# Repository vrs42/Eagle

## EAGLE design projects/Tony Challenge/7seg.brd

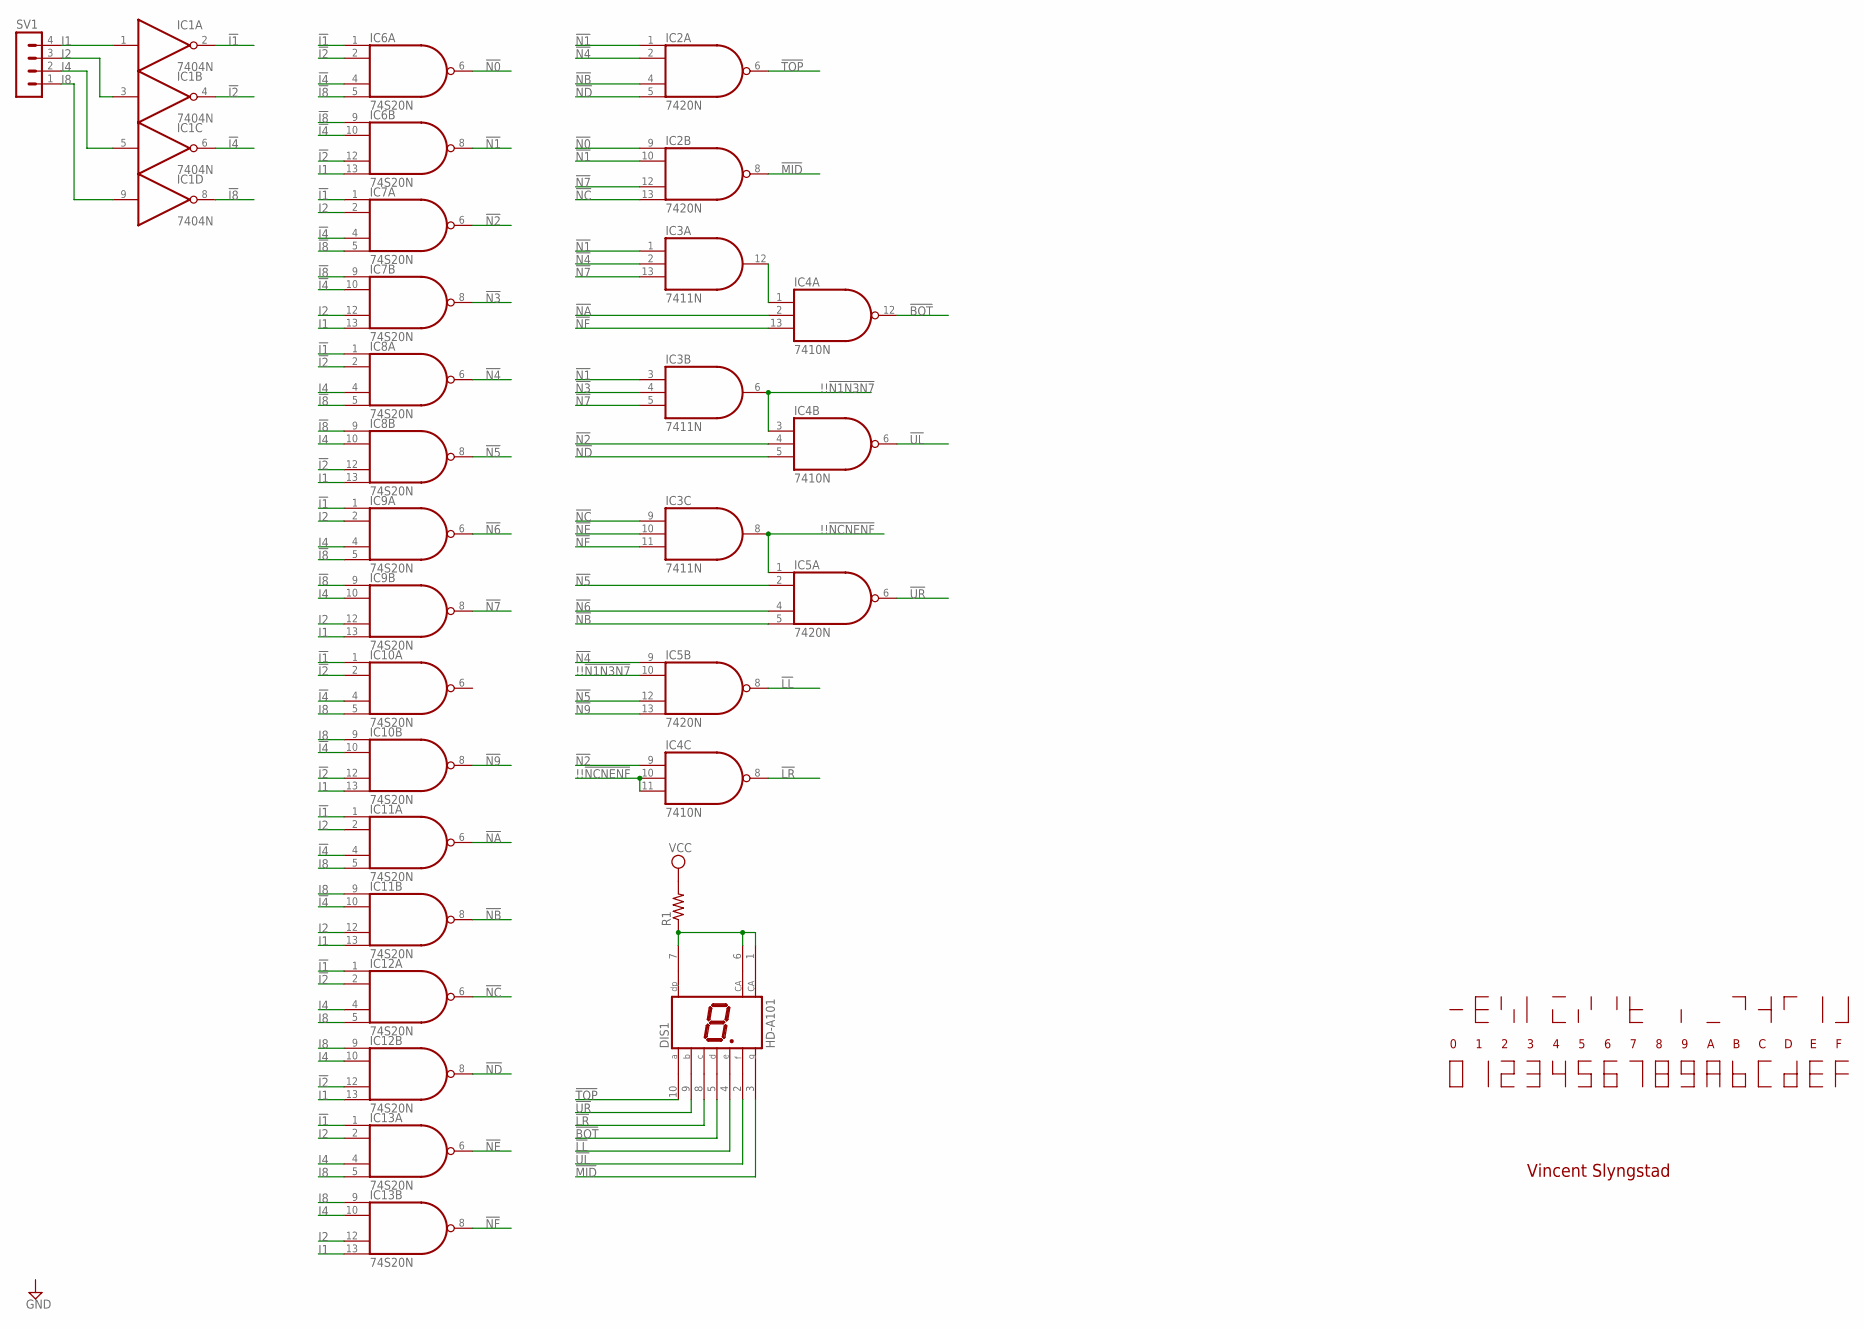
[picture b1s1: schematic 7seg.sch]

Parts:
DIS1: HD-A101; HDSP-A
IC1: 7404N; DIL14
IC2, IC5: 7420N; DIL14
IC3: 7411N; DIL14
IC4: 7410N; DIL14
IC6, IC7, IC8, IC9, IC10, IC11, IC12, IC13: 74S20N; DIL14
R1: R-US_0207/10; 0207/10
SV1: MA04-1

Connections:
!!!N1N3N7: IC3.6 (O), IC4.3 (I0), IC5.10 (I1)
!!!NCNENF: IC3.8 (O), IC4.10 (I1), IC4.11 (I2), IC5.1 (I0)
!BOT: DIS1.5 (D), IC4.12 (O)
!I1: IC1.2 (O), IC6.1 (I0), IC7.1 (I0), IC8.1 (I0), IC9.1 (I0), IC10.1 (I0), IC11.1 (I0), IC12.1 (I0), IC13.1 (I0)
!I2: IC1.4 (O), IC6.2 (I1), IC6.12 (I2), IC8.2 (I1), IC8.12 (I2), IC10.2 (I1), IC10.12 (I2), IC12.2 (I1), IC12.12 (I2)
!I4: IC1.6 (O), IC6.4 (I2), IC6.10 (I1), IC7.4 (I2), IC7.10 (I1), IC10.4 (I2), IC10.10 (I1), IC11.4 (I2), IC11.10 (I1)
!I8: IC1.8 (O), IC6.5 (I3), IC6.9 (I0), IC7.5 (I3), IC7.9 (I0), IC8.5 (I3), IC8.9 (I0), IC9.5 (I3), IC9.9 (I0)
!LL: DIS1.4 (E), IC5.8 (O)
!LR: DIS1.8 (C), IC4.8 (O)
!MID: DIS1.3 (G), IC2.8 (O)
!N0: IC2.9 (I0), IC6.6 (O)
!N1: IC2.1 (I0), IC2.10 (I1), IC3.1 (I0), IC3.3 (I0), IC6.8 (O)
!N2: IC4.4 (I1), IC4.9 (I0), IC7.6 (O)
!N3: IC3.4 (I1), IC7.8 (O)
!N4: IC2.2 (I1), IC3.2 (I1), IC5.9 (I0), IC8.6 (O)
!N5: IC5.2 (I1), IC5.12 (I2), IC8.8 (O)
!N6: IC5.4 (I2), IC9.6 (O)
!N7: IC2.12 (I2), IC3.5 (I2), IC3.13 (I2), IC9.8 (O)
!N9: IC5.13 (I3), IC10.8 (O)
!NA: IC4.2 (I1), IC11.6 (O)
!NB: IC2.4 (I2), IC5.5 (I3), IC11.8 (O)
!NC: IC2.13 (I3), IC3.9 (I0), IC12.6 (O)
!ND: IC2.5 (I3), IC4.5 (I2), IC12.8 (O)
!NE: IC3.10 (I1), IC13.6 (O)
!NF: IC3.11 (I2), IC4.13 (I2), IC13.8 (O)
!TOP: DIS1.10 (A), IC2.6 (O)
!UL: DIS1.2 (F), IC4.6 (O)
!UR: DIS1.9 (B), IC5.6 (O)
GND: IC1.7 (GND), IC2.7 (GND), IC3.7 (GND), IC4.7 (GND), IC5.7 (GND), IC6.7 (GND), IC7.7 (GND), IC8.7 (GND), IC9.7 (GND), IC10.7 (GND), IC11.7 (GND), IC12.7 (GND), IC13.7 (GND)
I1: IC1.1 (I), IC6.13 (I3), IC7.13 (I3), IC8.13 (I3), IC9.13 (I3), IC10.13 (I3), IC11.13 (I3), IC12.13 (I3), IC13.13 (I3), SV1.4
I2: IC1.3 (I), IC7.2 (I1), IC7.12 (I2), IC9.2 (I1), IC9.12 (I2), IC11.2 (I1), IC11.12 (I2), IC13.2 (I1), IC13.12 (I2), SV1.3
I4: IC1.5 (I), IC8.4 (I2), IC8.10 (I1), IC9.4 (I2), IC9.10 (I1), IC12.4 (I2), IC12.10 (I1), IC13.4 (I2), IC13.10 (I1), SV1.2
I8: IC1.9 (I), IC10.5 (I3), IC10.9 (I0), IC11.5 (I3), IC11.9 (I0), IC12.5 (I3), IC12.9 (I0), IC13.5 (I3), IC13.9 (I0), SV1.1
unnamed: IC3.12 (O), IC4.1 (I0)
unnamed: DIS1.1 (CA), DIS1.6 (CA), DIS1.7 (DP), R1.1
VCC: IC1.14 (VCC), IC2.14 (VCC), IC3.14 (VCC), IC4.14 (VCC), IC5.14 (VCC), IC6.14 (VCC), IC7.14 (VCC), IC8.14 (VCC), IC9.14 (VCC), IC10.14 (VCC), IC11.14 (VCC), IC12.14 (VCC), IC13.14 (VCC), R1.2

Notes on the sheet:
Vincent Slyngstad

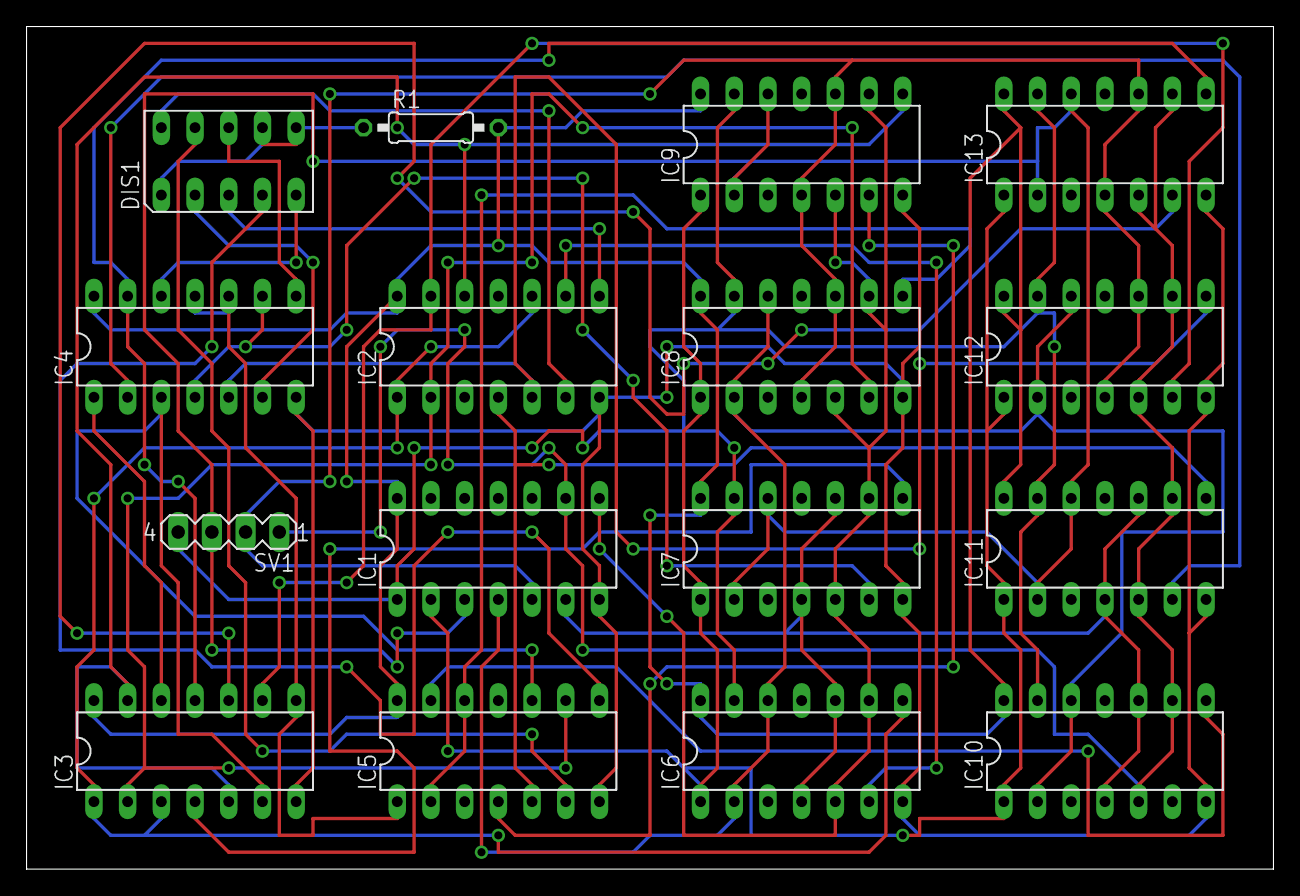
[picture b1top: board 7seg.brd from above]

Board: 2 copper layers, 94.0 x 63.5 mm, 16 parts (0 on the bottom side), 36 nets.

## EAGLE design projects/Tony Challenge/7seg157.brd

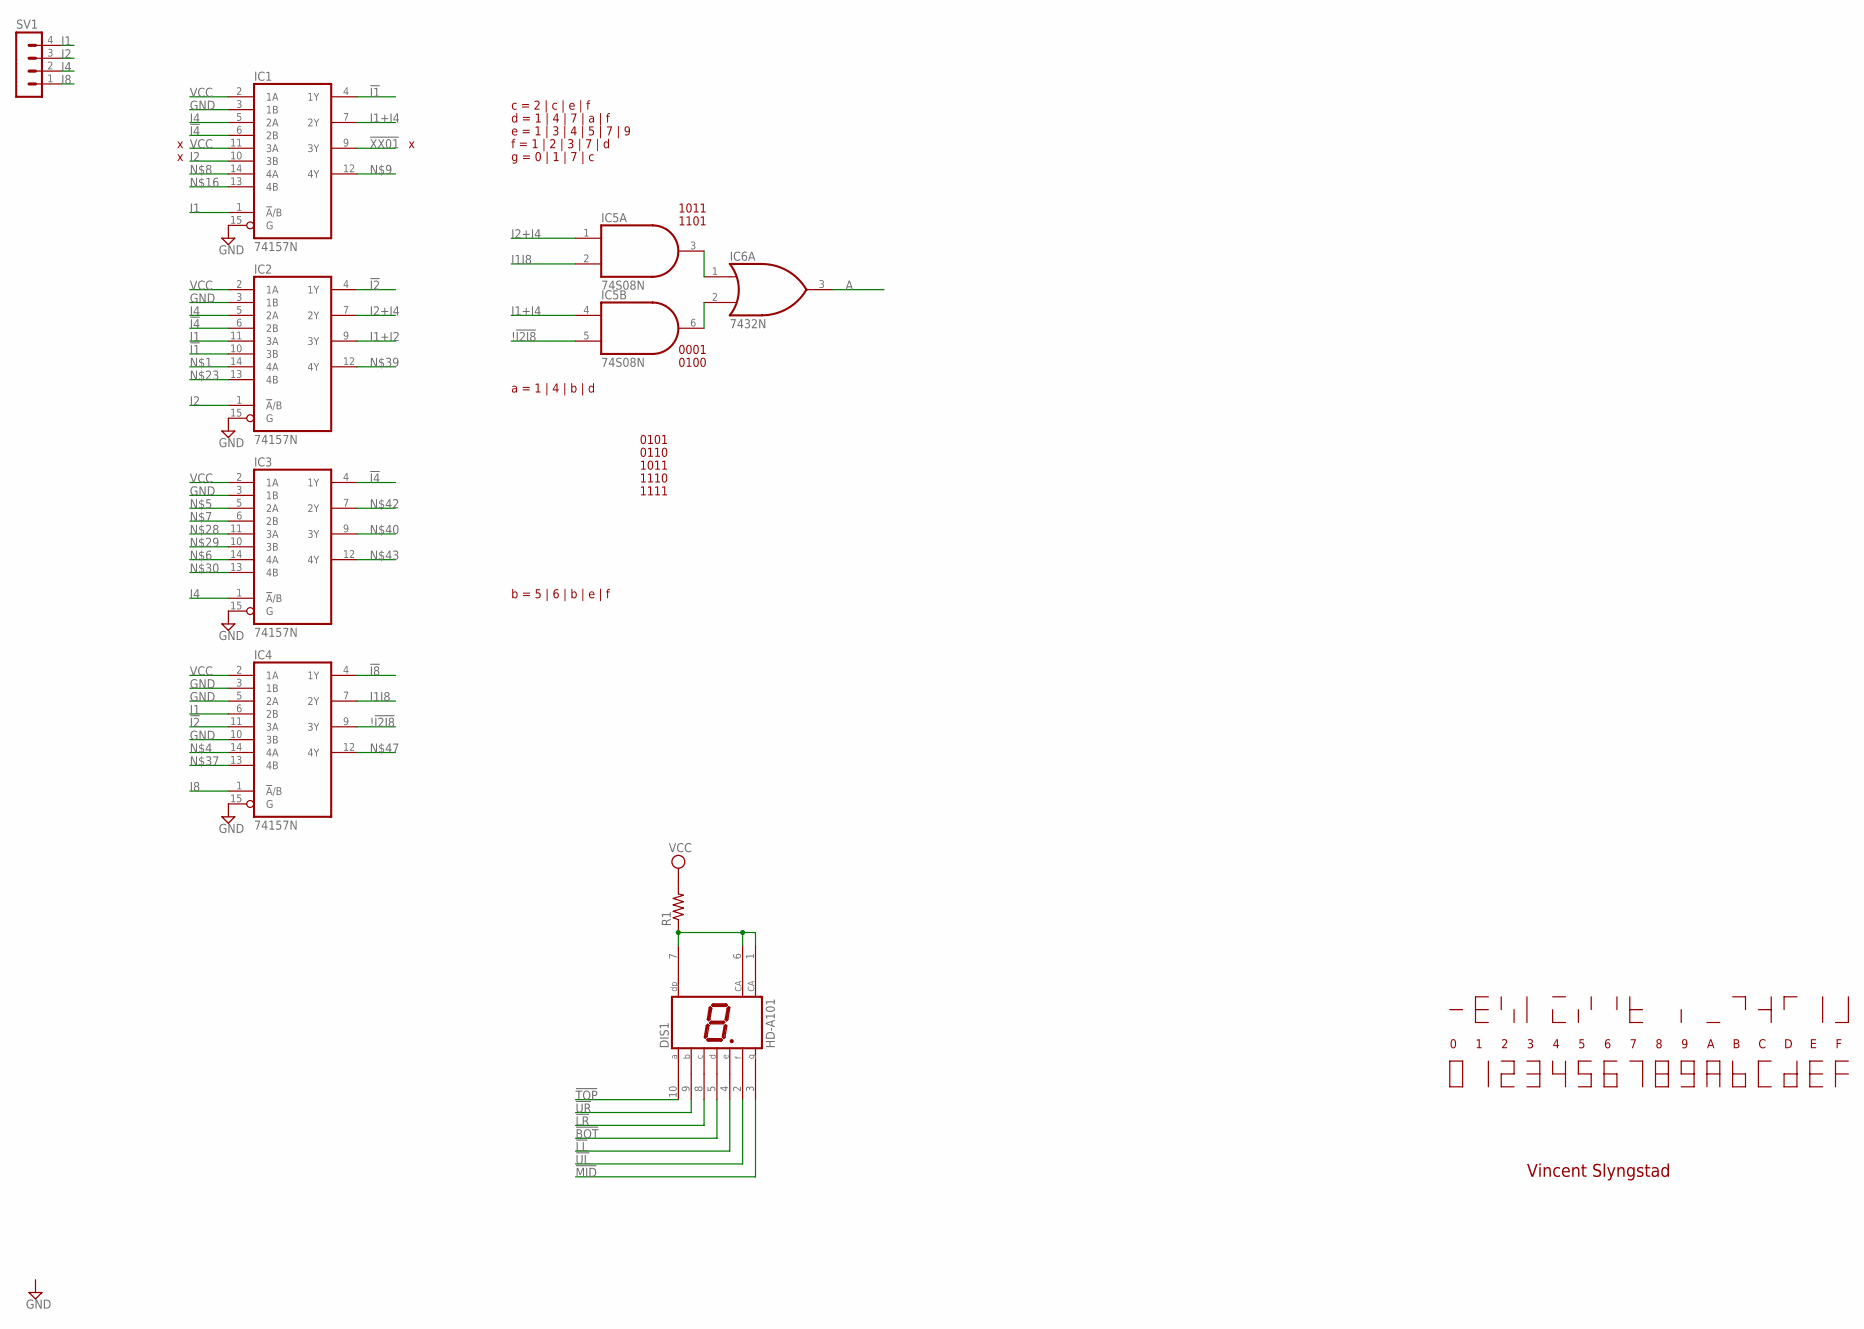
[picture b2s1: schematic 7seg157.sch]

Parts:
DIS1: HD-A101; HDSP-A
IC1, IC2, IC3, IC4: 74157N; DIL16
IC5: 74S08N; DIL14
IC6: 7432N; DIL14
R1: R-US_0207/10; 0207/10
SV1: MA04-1

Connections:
!!I2I8: IC4.9 (3Y), IC5.5 (I1)
!BOT: DIS1.5 (D)
!I1: IC1.4 (1Y), IC2.10 (3B)
!I2: IC2.4 (1Y), IC4.11 (3A)
!I4: IC1.6 (2B), IC2.6 (2B), IC3.4 (1Y)
!I8: IC4.4 (1Y)
!LL: DIS1.4 (E)
!LR: DIS1.8 (C)
!MID: DIS1.3 (G)
!TOP: DIS1.10 (A)
!UL: DIS1.2 (F)
!UR: DIS1.9 (B)
!XX01: IC1.9 (3Y)
A: IC6.3 (O)
GND: IC1.3 (1B), IC1.8 (GND), IC1.15 (G), IC2.3 (1B), IC2.8 (GND), IC2.15 (G), IC3.3 (1B), IC3.8 (GND), IC3.15 (G), IC4.3 (1B), IC4.5 (2A), IC4.8 (GND), IC4.10 (3B), IC4.15 (G), IC5.7 (GND), IC6.7 (GND)
I1: IC1.1 (!A!/B), IC2.11 (3A), IC4.6 (2B), SV1.4
I1+I2: IC2.9 (3Y)
I1+I4: IC1.7 (2Y), IC5.4 (I0)
I1I8: IC4.7 (2Y), IC5.2 (I1)
I2: IC1.10 (3B), IC2.1 (!A!/B), SV1.3
I2+I4: IC2.7 (2Y), IC5.1 (I0)
I4: IC1.5 (2A), IC2.5 (2A), IC3.1 (!A!/B), SV1.2
I8: IC4.1 (!A!/B), SV1.1
unnamed: DIS1.1 (CA), DIS1.6 (CA), DIS1.7 (DP), R1.1
unnamed: IC5.3 (O), IC6.1 (I0)
unnamed: IC5.6 (O), IC6.2 (I1)
VCC: IC1.2 (1A), IC1.11 (3A), IC1.16 (VCC), IC2.2 (1A), IC2.16 (VCC), IC3.2 (1A), IC3.16 (VCC), IC4.2 (1A), IC4.16 (VCC), IC5.14 (VCC), IC6.14 (VCC), R1.2

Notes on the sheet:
Vincent Slyngstad
a = 1 | 4 | b | d
b = 5 | 6 | b | e | f
c = 2 | c | e | f
d = 1 | 4 | 7 | a | f
e = 1 | 3 | 4 | 5 | 7 | 9
f = 1 | 2 | 3 | 7 | d
g = 0 | 1 | 7 | c
0001
0100
1011
1101
0101
0110
1110
1111

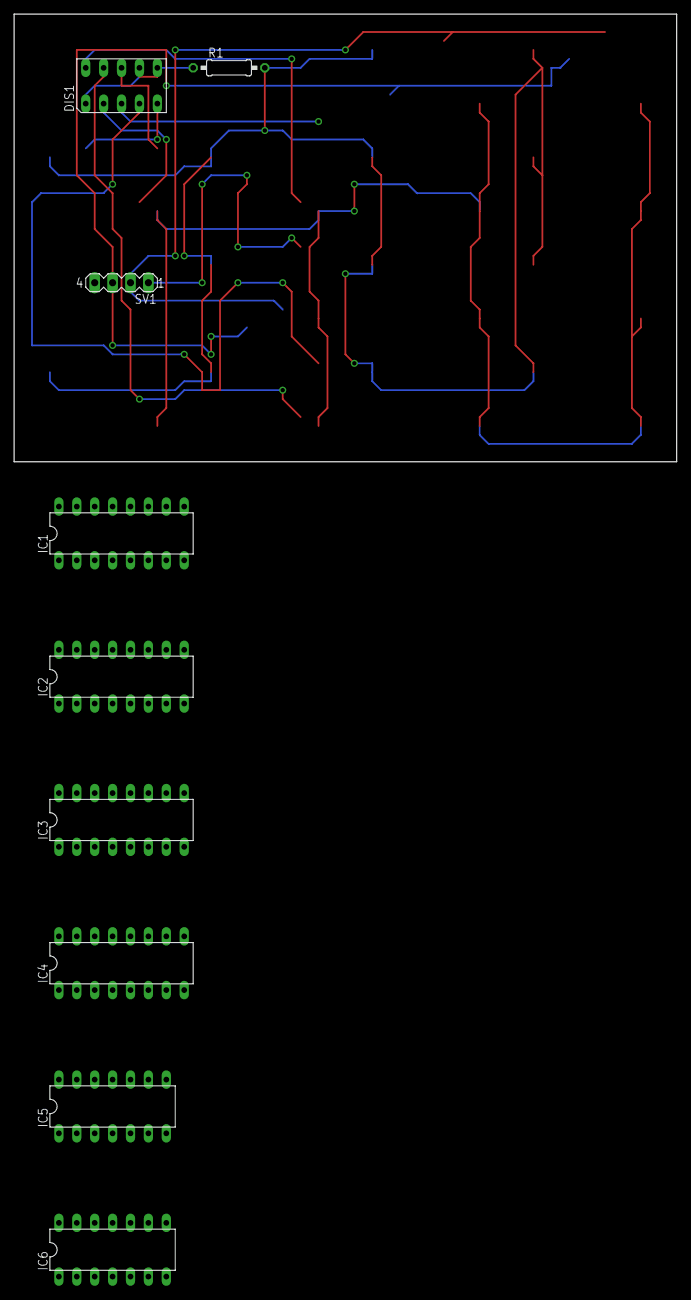
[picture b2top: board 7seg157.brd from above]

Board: 2 copper layers, 94.0 x 63.5 mm, 9 parts (0 on the bottom side), 16 nets.

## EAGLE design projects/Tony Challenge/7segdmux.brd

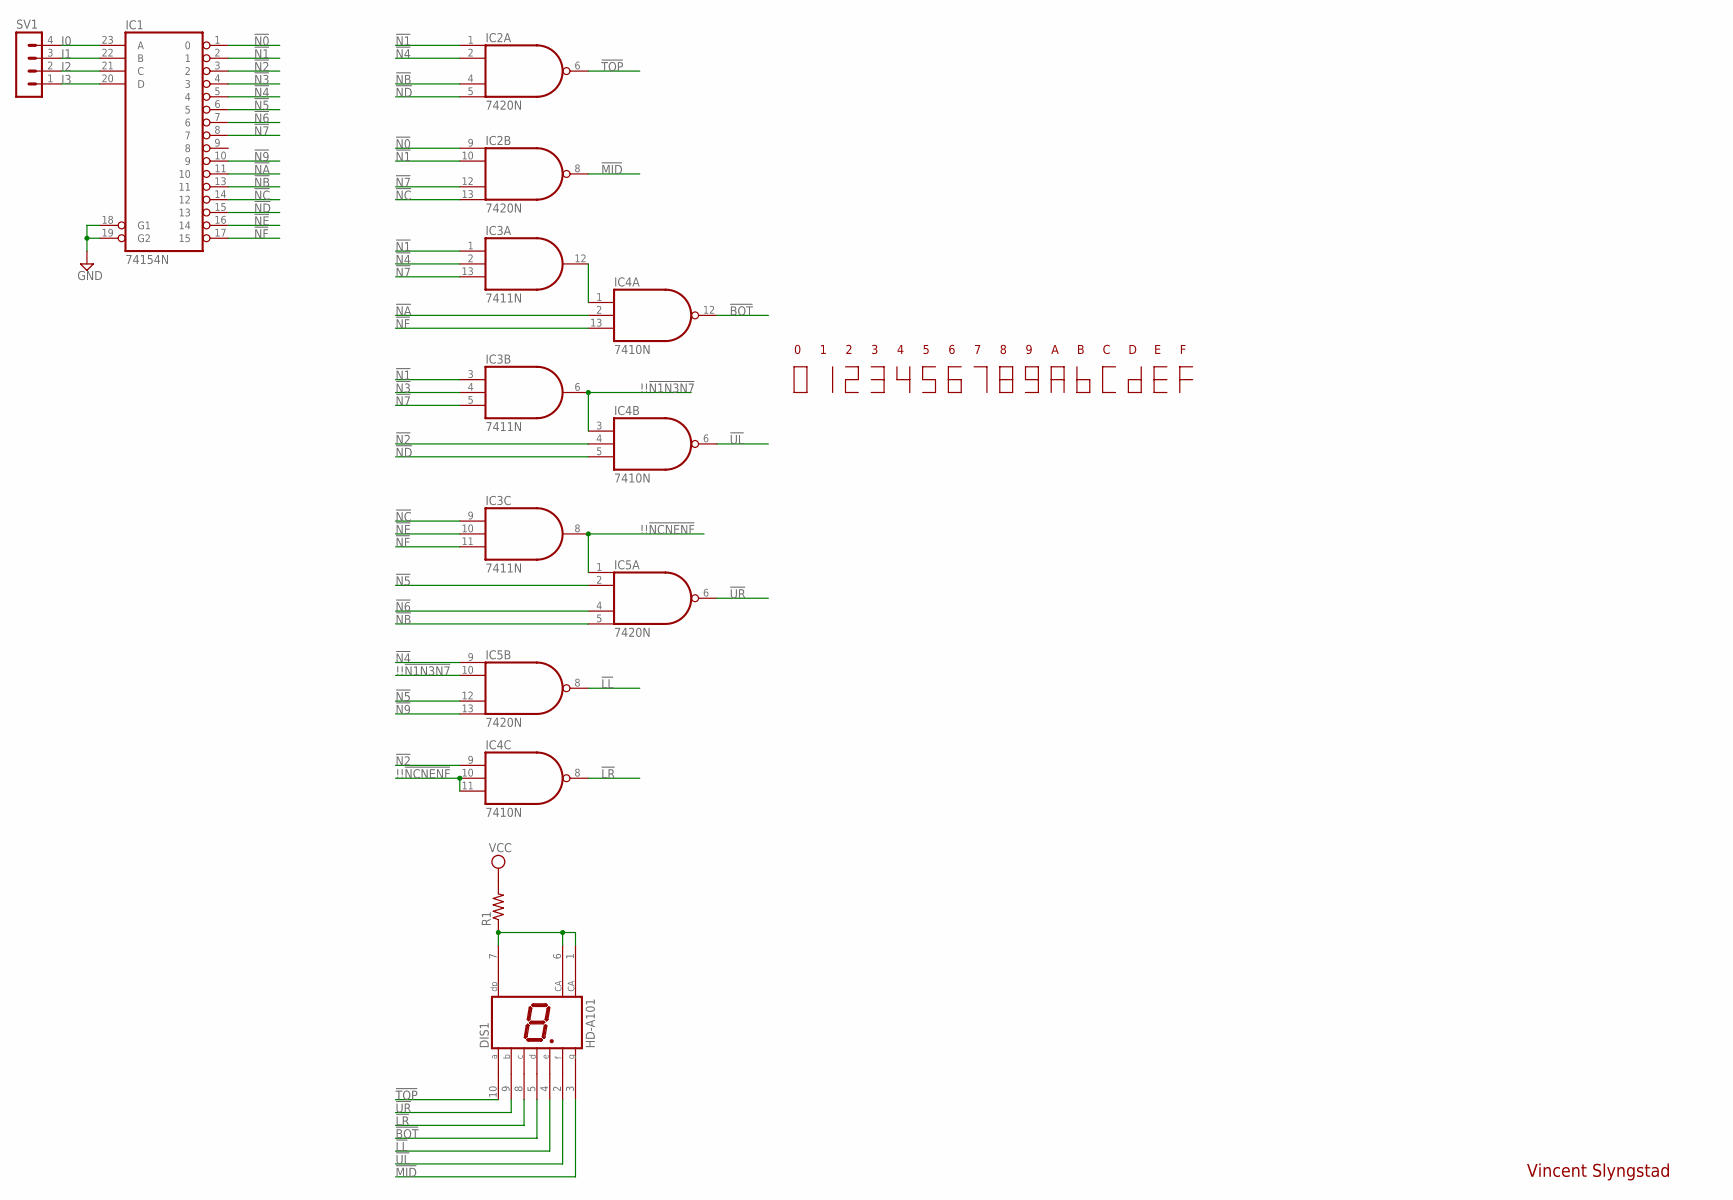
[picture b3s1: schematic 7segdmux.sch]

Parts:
DIS1: HD-A101; HDSP-A
IC1: 74154N; DIL24-6
IC2, IC5: 7420N; DIL14
IC3: 7411N; DIL14
IC4: 7410N; DIL14
R1: R-US_0207/10; 0207/10
SV1: MA04-1

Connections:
!!!N1N3N7: IC3.6 (O), IC4.3 (I0), IC5.10 (I1)
!!!NCNENF: IC3.8 (O), IC4.10 (I1), IC4.11 (I2), IC5.1 (I0)
!BOT: DIS1.5 (D), IC4.12 (O)
!LL: DIS1.4 (E), IC5.8 (O)
!LR: DIS1.8 (C), IC4.8 (O)
!MID: DIS1.3 (G), IC2.8 (O)
!N0: IC1.1 (0), IC2.9 (I0)
!N1: IC1.2 (1), IC2.1 (I0), IC2.10 (I1), IC3.1 (I0), IC3.3 (I0)
!N2: IC1.3 (2), IC4.4 (I1), IC4.9 (I0)
!N3: IC1.4 (3), IC3.4 (I1)
!N4: IC1.5 (4), IC2.2 (I1), IC3.2 (I1), IC5.9 (I0)
!N5: IC1.6 (5), IC5.2 (I1), IC5.12 (I2)
!N6: IC1.7 (6), IC5.4 (I2)
!N7: IC1.8 (7), IC2.12 (I2), IC3.5 (I2), IC3.13 (I2)
!N9: IC1.10 (9), IC5.13 (I3)
!NA: IC1.11 (10), IC4.2 (I1)
!NB: IC1.13 (11), IC2.4 (I2), IC5.5 (I3)
!NC: IC1.14 (12), IC2.13 (I3), IC3.9 (I0)
!ND: IC1.15 (13), IC2.5 (I3), IC4.5 (I2)
!NE: IC1.16 (14), IC3.10 (I1)
!NF: IC1.17 (15), IC3.11 (I2), IC4.13 (I2)
!TOP: DIS1.10 (A), IC2.6 (O)
!UL: DIS1.2 (F), IC4.6 (O)
!UR: DIS1.9 (B), IC5.6 (O)
GND: IC1.12 (GND), IC1.18 (G1), IC1.19 (G2), IC2.7 (GND), IC3.7 (GND), IC4.7 (GND), IC5.7 (GND)
I0: IC1.23 (A), SV1.4
I1: IC1.22 (B), SV1.3
I2: IC1.21 (C), SV1.2
I3: IC1.20 (D), SV1.1
unnamed: IC3.12 (O), IC4.1 (I0)
unnamed: DIS1.1 (CA), DIS1.6 (CA), DIS1.7 (DP), R1.1
VCC: IC1.24 (VCC), IC2.14 (VCC), IC3.14 (VCC), IC4.14 (VCC), IC5.14 (VCC), R1.2

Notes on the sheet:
Vincent Slyngstad

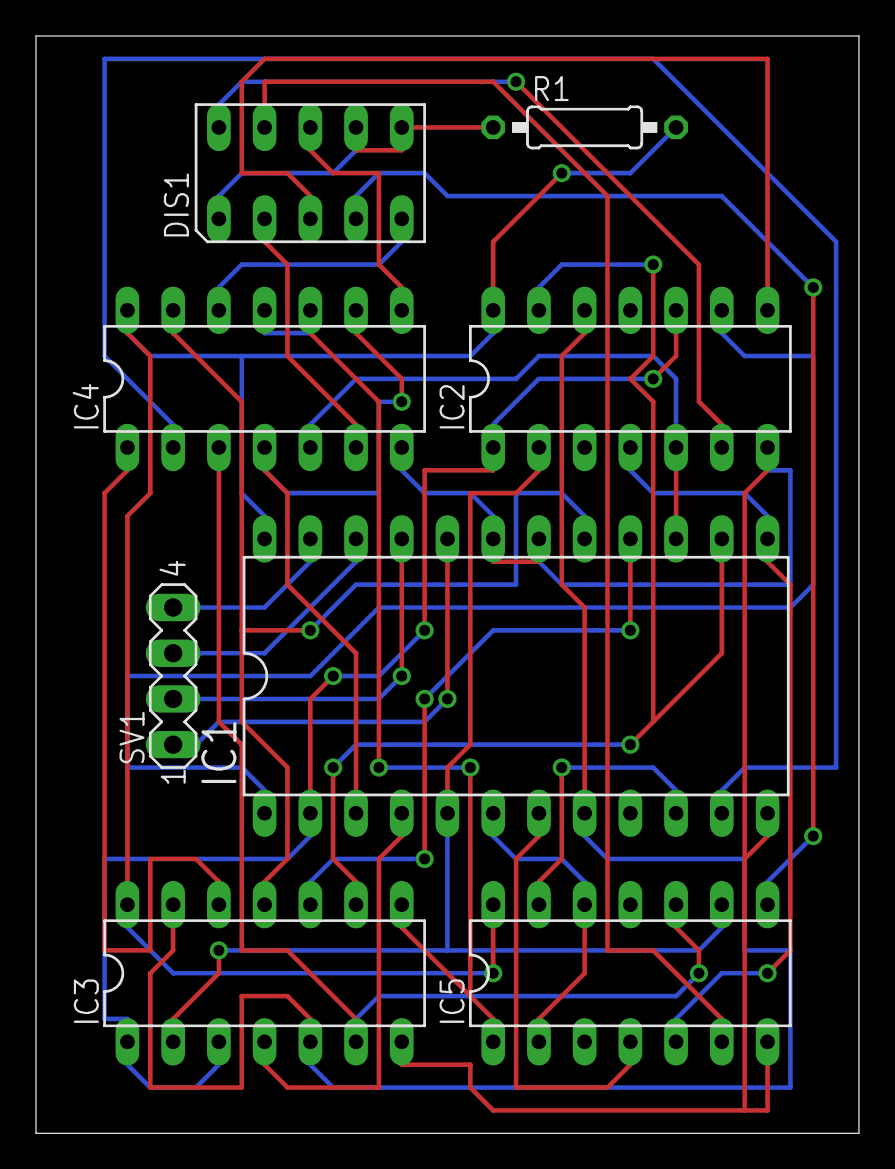
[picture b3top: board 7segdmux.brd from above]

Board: 2 copper layers, 45.7 x 61.0 mm, 8 parts (0 on the bottom side), 32 nets.

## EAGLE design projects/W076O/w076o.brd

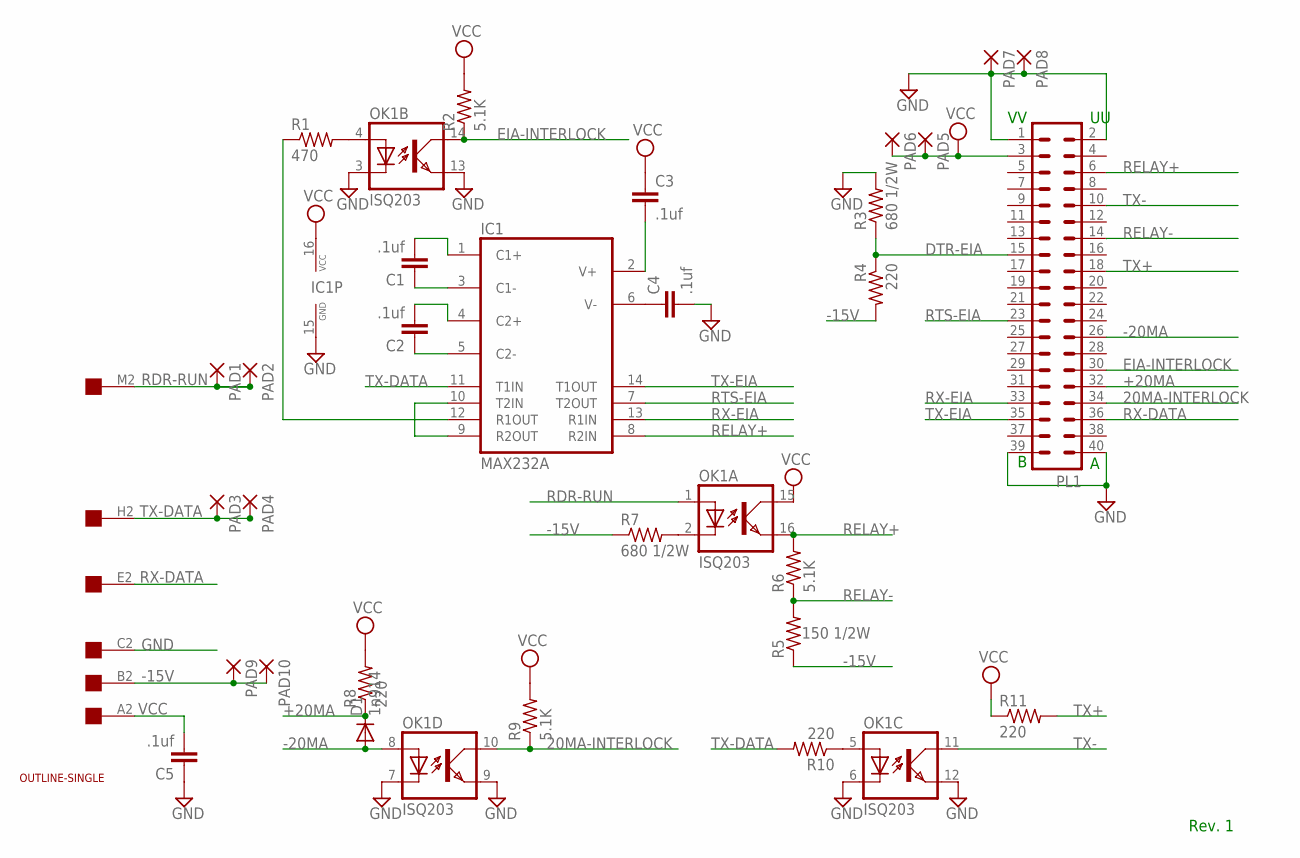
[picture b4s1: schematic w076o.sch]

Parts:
C1, C2, C3, C4, C5: .1uf; C050-025X075
D1: 1n914; DO41-10
IC1: MAX232A; DIL16
OK1: ISQ203; DIL16
PAD1, PAD2, PAD3, PAD4, PAD5, PAD6, PAD7, PAD8, PAD9, PAD10: 1,6/0,8
PL1: 40H
R1: 470; 0207/10
R2, R6, R9: 5.1K; 0207/10
R3, R7: 680 1/2W; 0207/12
R4, R8, R10, R11: 220; 0207/10
R5: 150 1/2W; 0207/12
U$1: EDGE-2CONNECTOR; EDGE-CON2
U$2: OUTLINE-SINGLE; SINGLE

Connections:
20MA-INTERLOCK: OK1.10 (COL), PL1.34, R9.1
+20MA: D1.C, PL1.32, R8.1
-15V: PAD9.1, PAD10.1, R4.2, R5.1, R7.1, U$1.B2
-20MA: D1.A, OK1.8 (A), PL1.26
DTR-EIA: PL1.15, R3.1, R4.1
EIA-INTERLOCK: OK1.14 (COL), PL1.30, R2.1
GND: C4.2, C5.1, IC1.15 (GND), OK1.3 (C), OK1.6 (C), OK1.7 (C), OK1.9 (EMIT), OK1.12 (EMIT), OK1.13 (EMIT), PAD7.1, PAD8.1, PL1.1, PL1.2, PL1.39, PL1.40, R3.2, U$1.C2
unnamed: C2.1, IC1.5 (C2-)
unnamed: C2.2, IC1.4 (C2+)
unnamed: C1.2, IC1.1 (C1+)
unnamed: C1.1, IC1.3 (C1-)
unnamed: OK1.2 (C), R7.2
unnamed: IC1.9 (R2OUT), IC1.10 (T2IN)
unnamed: IC1.12 (R1OUT), R1.1
unnamed: C3.2, IC1.2 (V+)
unnamed: C4.1, IC1.6 (V-)
unnamed: OK1.4 (A), R1.2
unnamed: OK1.5 (A), R10.1
RDR-RUN: OK1.1 (A), PAD1.1, PAD2.1, U$1.M2
RELAY+: IC1.8 (R2IN), OK1.16 (EMIT), PL1.6, R6.2
RELAY-: PL1.14, R5.2, R6.1
RTS-EIA: IC1.7 (T2OUT), PL1.23
RX-DATA: PL1.36, U$1.E2
RX-EIA: IC1.13 (R1IN), PL1.33
TX+: PL1.18, R11.2
TX-: OK1.11 (COL), PL1.10
TX-DATA: IC1.11 (T1IN), PAD3.1, PAD4.1, R10.2, U$1.H2
TX-EIA: IC1.14 (T1OUT), PL1.35
VCC: C3.1, C5.2, IC1.16 (VCC), OK1.15 (COL), PAD5.1, PAD6.1, PL1.3, R2.2, R8.2, R9.2, R11.1, U$1.A2

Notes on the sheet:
Rev. 1

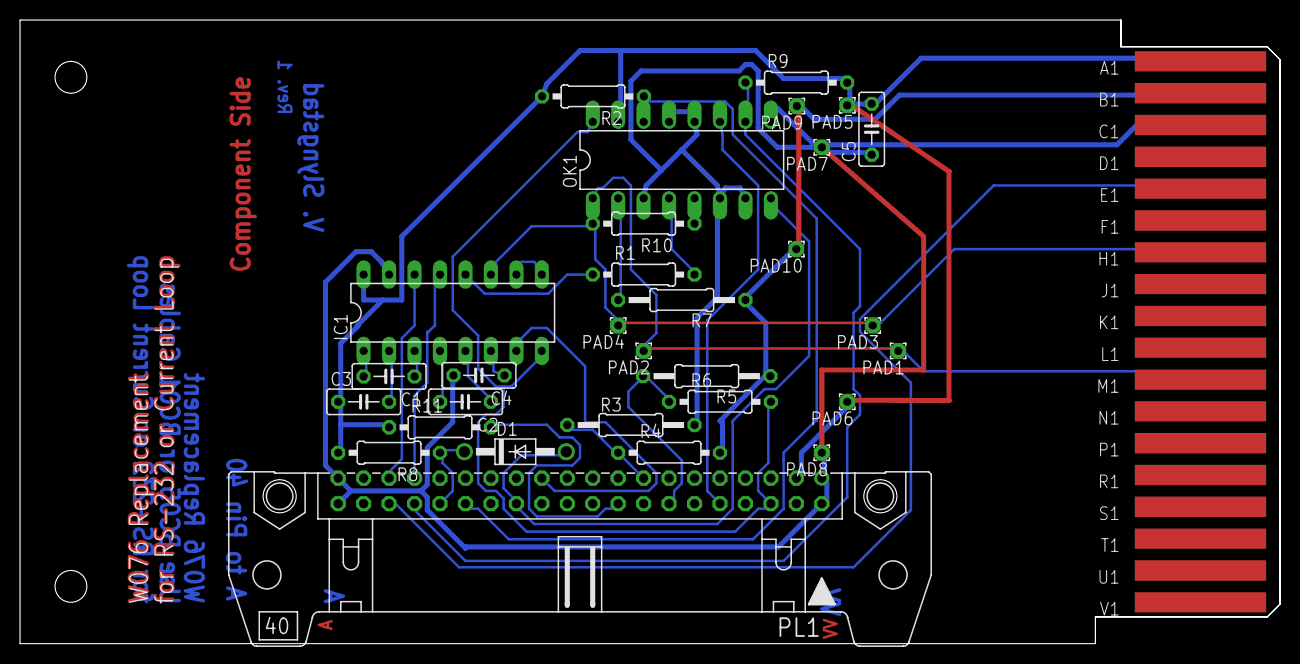
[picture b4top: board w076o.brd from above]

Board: 2 copper layers, 125.7 x 62.2 mm, 32 parts (0 on the bottom side), 29 nets.

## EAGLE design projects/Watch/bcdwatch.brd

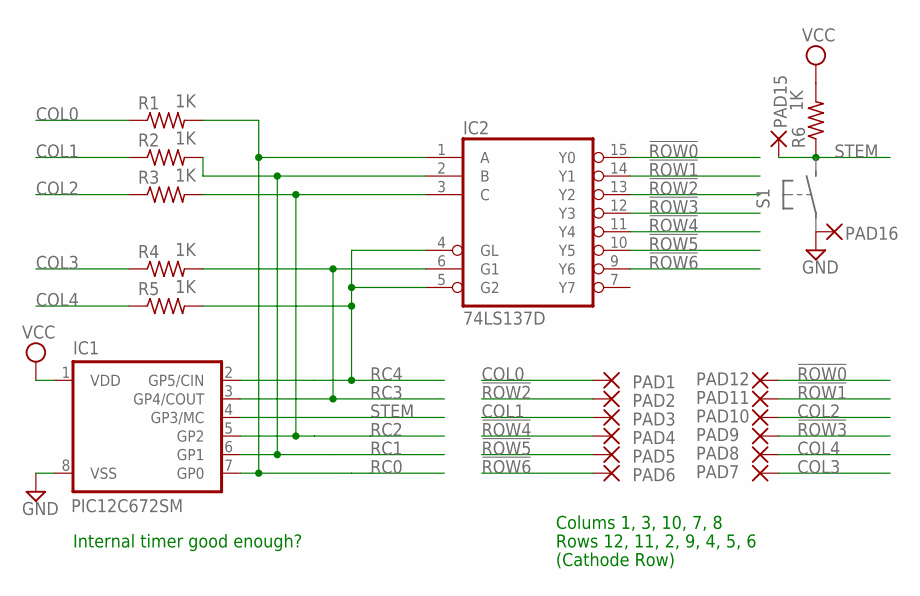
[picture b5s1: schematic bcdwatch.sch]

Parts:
IC1: PIC12C672SM; SO-08M
IC2: 74LS137D; SO16
PAD1, PAD2, PAD3, PAD4, PAD5, PAD6, PAD7, PAD8, PAD9, PAD10, PAD11, PAD12, PAD15, PAD16: SMD2; SMD1,27-2,54
R1, R2, R3, R4, R5, R6: 1K; R0805

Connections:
!ROW0: IC2.15 (Y0), PAD12.1
!ROW1: IC2.14 (Y1), PAD11.1
!ROW2: IC2.13 (Y2), PAD2.1
!ROW3: IC2.12 (Y3), PAD9.1
!ROW4: IC2.11 (Y4), PAD4.1
!ROW5: IC2.10 (Y5), PAD5.1
!ROW6: IC2.9 (Y6), PAD6.1
COL0: PAD1.1, R1.1
COL1: PAD3.1, R2.1
COL2: PAD10.1, R3.1
COL3: PAD7.1, R4.1
COL4: PAD8.1, R5.1
GND: IC1.8 (VSS), IC2.8 (GND), PAD16.1
RC0: IC1.7 (GP0), IC2.1 (A), R1.2
RC1: IC1.6 (GP1), IC2.2 (B), R2.2
RC2: IC1.5 (GP2), IC2.3 (C), R3.2
RC3: IC1.3 (GP4/COUT), IC2.6 (G1), R4.2
RC4: IC1.2 (GP5/CIN), IC2.4 (GL), IC2.5 (G2), R5.2
STEM: IC1.4 (GP3/MC), PAD15.1, R6.1
VCC: IC1.1 (VDD), IC2.16 (VCC), R6.2

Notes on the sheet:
Colums 1, 3, 10, 7, 8
Rows 12, 11, 2, 9, 4, 5, 6
Internal timer good enough?
(Cathode Row)

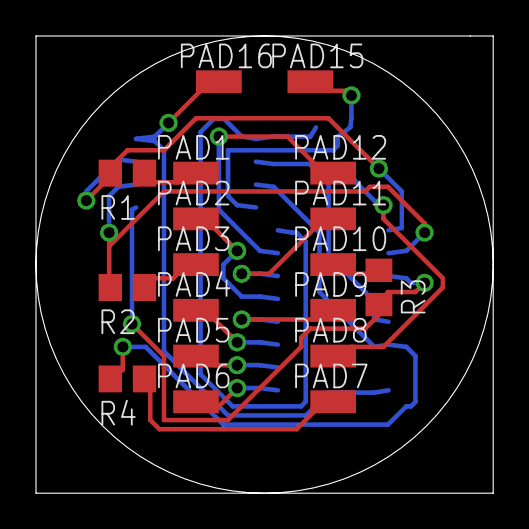
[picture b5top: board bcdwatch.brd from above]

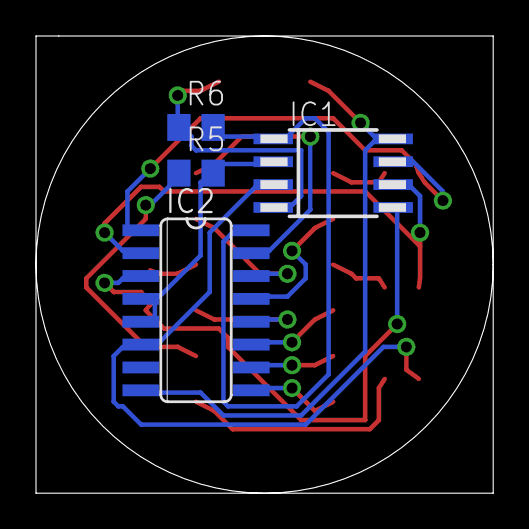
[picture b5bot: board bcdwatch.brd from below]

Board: 2 copper layers, 25.4 x 25.4 mm, 22 parts (4 on the bottom side), 20 nets.

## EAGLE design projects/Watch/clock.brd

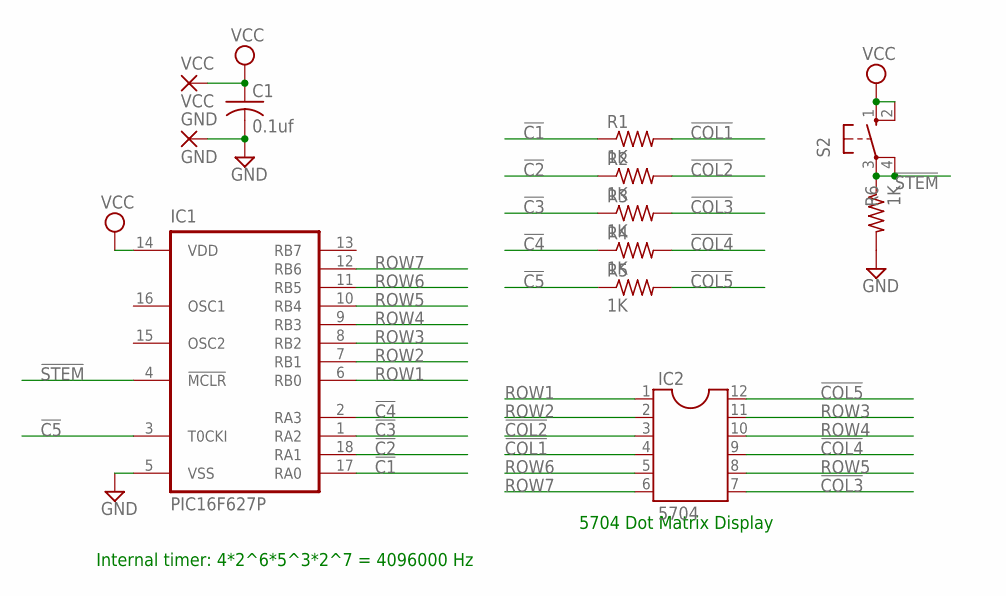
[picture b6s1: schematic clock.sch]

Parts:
C1: 0.1uf; C025-025X050
GND: GND; 1,6/0,8
IC1: PIC16F627P; DIL18
IC2: 5704; DIL12
R1, R2, R3, R4, R5, R6: 1K; 0207/10
S2: 10-XX; B3F-10XX
VCC: VCC; 1,6/0,8

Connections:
!C1: IC1.17 (RA0), R1.1
!C2: IC1.18 (RA1), R2.1
!C3: IC1.1 (RA2), R3.1
!C4: IC1.2 (RA3), R4.1
!C5: IC1.3 (T0CKI), R5.1
!COL1: IC2.4, R1.2
!COL2: IC2.3, R2.2
!COL3: IC2.7, R3.2
!COL4: IC2.9, R4.2
!COL5: IC2.12, R5.2
!STEM: IC1.4 (!MCLR), R6.1, S2.3, S2.4 (P1)
GND: C1.2, GND.1, IC1.5 (VSS), R6.2
ROW1: IC1.6 (RB0), IC2.1
ROW2: IC1.7 (RB1), IC2.2
ROW3: IC1.8 (RB2), IC2.11
ROW4: IC1.9 (RB3), IC2.10
ROW5: IC1.10 (RB4), IC2.8
ROW6: IC1.11 (RB5), IC2.5
ROW7: IC1.12 (RB6), IC2.6
VCC: C1.1, IC1.14 (VDD), S2.1 (S), S2.2 (S1), VCC.1

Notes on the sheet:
Internal timer: 4*2^6*5^3*2^7 = 4096000 Hz
5704 Dot Matrix Display

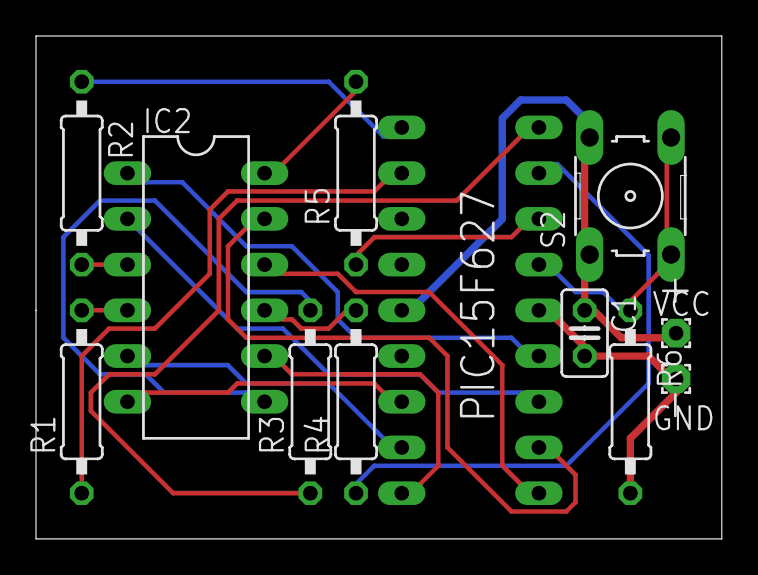
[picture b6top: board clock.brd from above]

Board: 2 copper layers, 38.1 x 27.9 mm, 12 parts (1 on the bottom side), 20 nets.
